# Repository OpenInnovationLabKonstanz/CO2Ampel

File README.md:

# CO2Ampel
A device for visual representation of  CO2 concentraition in the air. Helps monitoring air quality in order to reduce the risk of COVID19 infections in closed rooms.

## Project Overview

ToDo: ...

## Hardware

The device consists of a CO2 sensor, connected to a ESP32-WROOM-32 as main controller. Three large LED arrays (red, yellow, green) are used as a indicator for air quality. In addition, a numeric display shows the current CO2 concentration in ppm.

### CO2 Sensor
Due to the bad availability of CO2 sensors during the COVID19 pandemic, multiple sensor types are supported.
* SenseAir S8 (UART)
* MH-Z19B (pin-compatible to the S8)
* Sensirion SCD30 (I2C)

### Environment Sensor
As an additional method of air quality measurement, a Bosch BME680 multi environmental sensor is used. 
It provides temperature, rel. humidity, air pressure and VOC (volatile organic compounds) measurement.

### Ambient Light Sensor
In order to adapt the display and LED brightness, a OPT3001 ambient light 

### Display
A 4-digit 7-segment display, driven by a TitanMicro TM1638 is used to display the current CO2 concentration (in ppm).

## PCB
The PCB is routed as a 2-layer PCB. Parts are only placed on the top side in order to facilitate mass production.
Layout files are provided as Eagle 6.4 .brd and .sch files.

## Software
The firmware for the ESP32 is written in Arduino, using the ESP32-Arduino support package.
It uses following external libraries:
* SparkFun SCD30 Library (ToDo: Link)
* ClosedCube OPT3001 Library (ToDo: Link)
* Adafruit Sensor Library (ToDo: Link)
* Adafruit BME680 Library (ToDo: Link)
* ...

## Mechanical
The housing is laser-cut from 3mm acrylic sheets. Use sheets with satin finish for better light dispersion (eg. TroGlass Satin).
DXF files for cutting and engraving are provided in *Mechanical*.

## Contact
Stefan Oechslein, Open Innovation Lab Konstanz, oil@htwg-konstanz.de

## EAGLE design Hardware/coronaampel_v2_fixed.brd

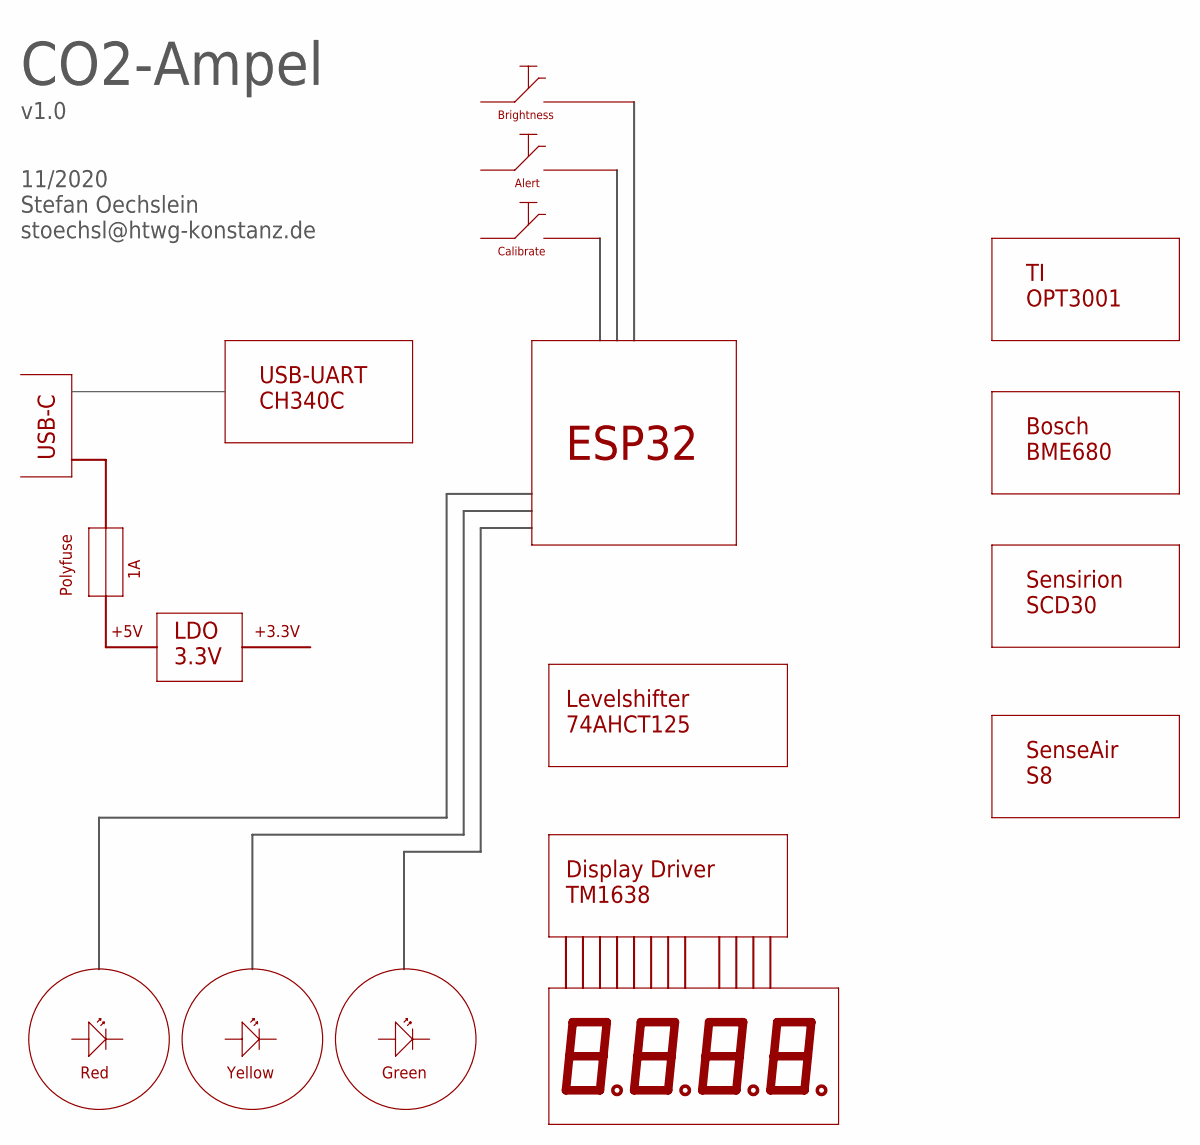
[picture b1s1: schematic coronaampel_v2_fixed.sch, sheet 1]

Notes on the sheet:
CO2-Ampel
ESP32
Sensirion SCD30
SenseAir S8
Bosch BME680
TI OPT3001
USB-UART CH340C
USB-C
LDO 3.3V
Display Driver TM1638
Levelshifter 74AHCT125
Polyfuse
+5V
+3.3V
Red
Yellow
Green
Alert
Calibrate
Brightness
v1.0
11/2020 Stefan Oechslein stoechsl@htwg-konstanz.de

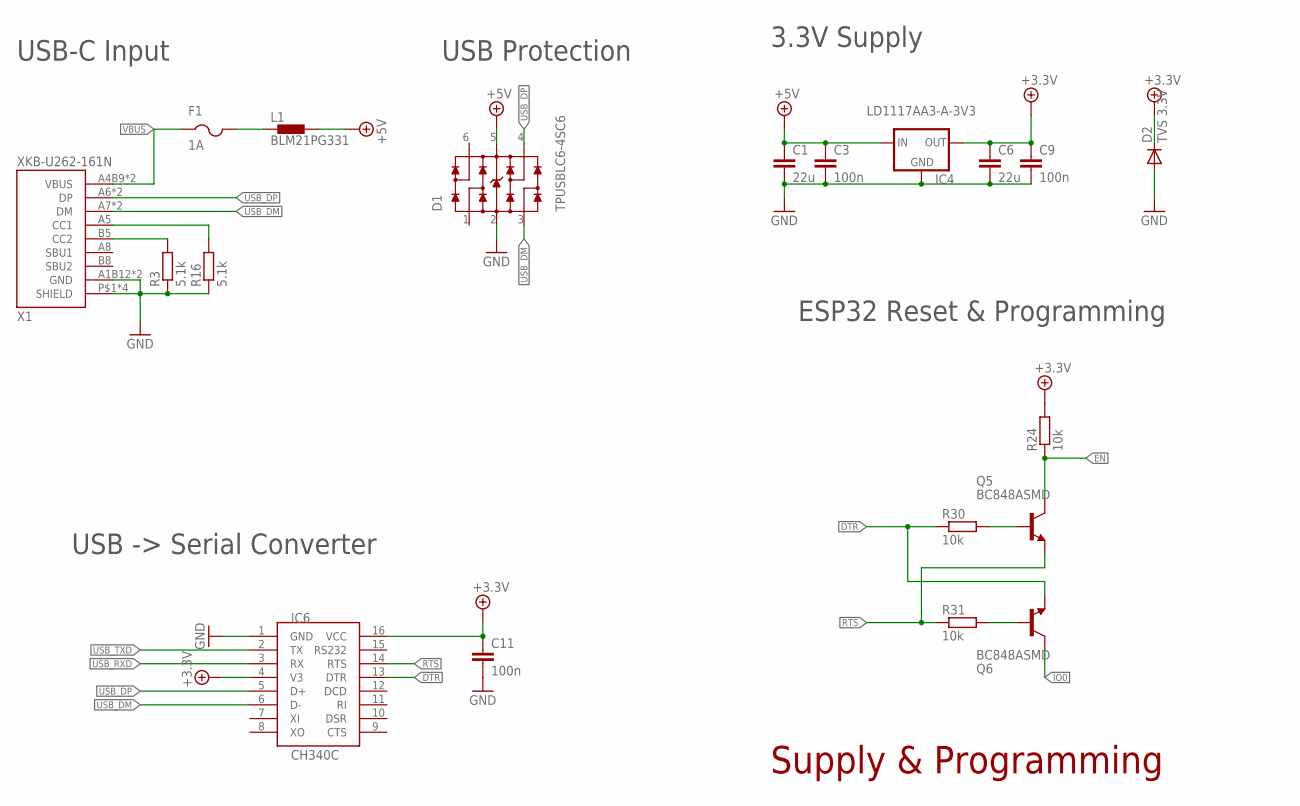
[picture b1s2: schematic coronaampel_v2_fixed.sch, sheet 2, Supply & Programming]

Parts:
C1, C6: 22u; C0805
C3, C9, C11: 100n; C0805
D1: TPUSBLC6-4SC6; WE-TVS_SOT23-6L
D2: TVS 3.3V; SOD123
F1: 1A; R0805
IC4: LD1117AA3-A-3V3; SOT223
IC6: CH340C; SOIC16
L1: BLM21PG331; 0805
Q5, Q6: BC848ASMD; SOT23
R3, R16: 5.1k; R0805
R24, R30, R31: 10k; R0805
X1: XKB-U262-161N; XKB_U262-161N

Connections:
+3,3V: C6.1, C9.1, C11.1, D2.C, IC4.2 (OUT), IC4.4 (OUT), IC6.4 (V3), IC6.16 (VCC), R24.2; also elsewhere on the board
+5V: C1.1, C3.1, D1.5 (VDD), IC4.3 (IN), L1.2; also elsewhere on the board
CC1: R16.2, X1.A5 (CC1)
CC2: R3.2, X1.B5 (CC2)
DTR: IC6.13 (DTR), Q6.2 (E), R30.1
EN: Q5.3 (C), R24.1; also elsewhere on the board
GND: C1.2, C3.2, C6.2, C9.2, C11.2, D1.2 (GND), D2.A, IC4.1 (GND), IC6.1 (GND), R3.1, R16.1, X1.A1B12 (GND), X1.B1A12 (GND), X1.P$1 (SHIELD), X1.P$2 (SHIELD), X1.P$3 (SHIELD), X1.P$4 (SHIELD); also elsewhere on the board
IO0: Q6.3 (C); also elsewhere on the board
unnamed: Q6.1 (B), R31.2
unnamed: Q5.1 (B), R30.2
RTS: IC6.14 (RTS), Q5.2 (E), R31.1
USB_DM: D1.3 (2), IC6.6 (D-), X1.A7 (DM), X1.B7 (DM)
USB_DP: D1.4 (3), IC6.5 (D+), X1.A6 (DP), X1.B6 (DP)
USB_RXD: IC6.3 (RX); also elsewhere on the board
USB_TXD: IC6.2 (TX); also elsewhere on the board
VBUS: F1.1, X1.A4B9 (VBUS), X1.B4A9 (VBUS)
VIN: F1.2, L1.1

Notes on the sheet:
USB -> Serial Converter
ESP32 Reset & Programming
USB-C Input
USB Protection
3.3V Supply
Supply & Programming

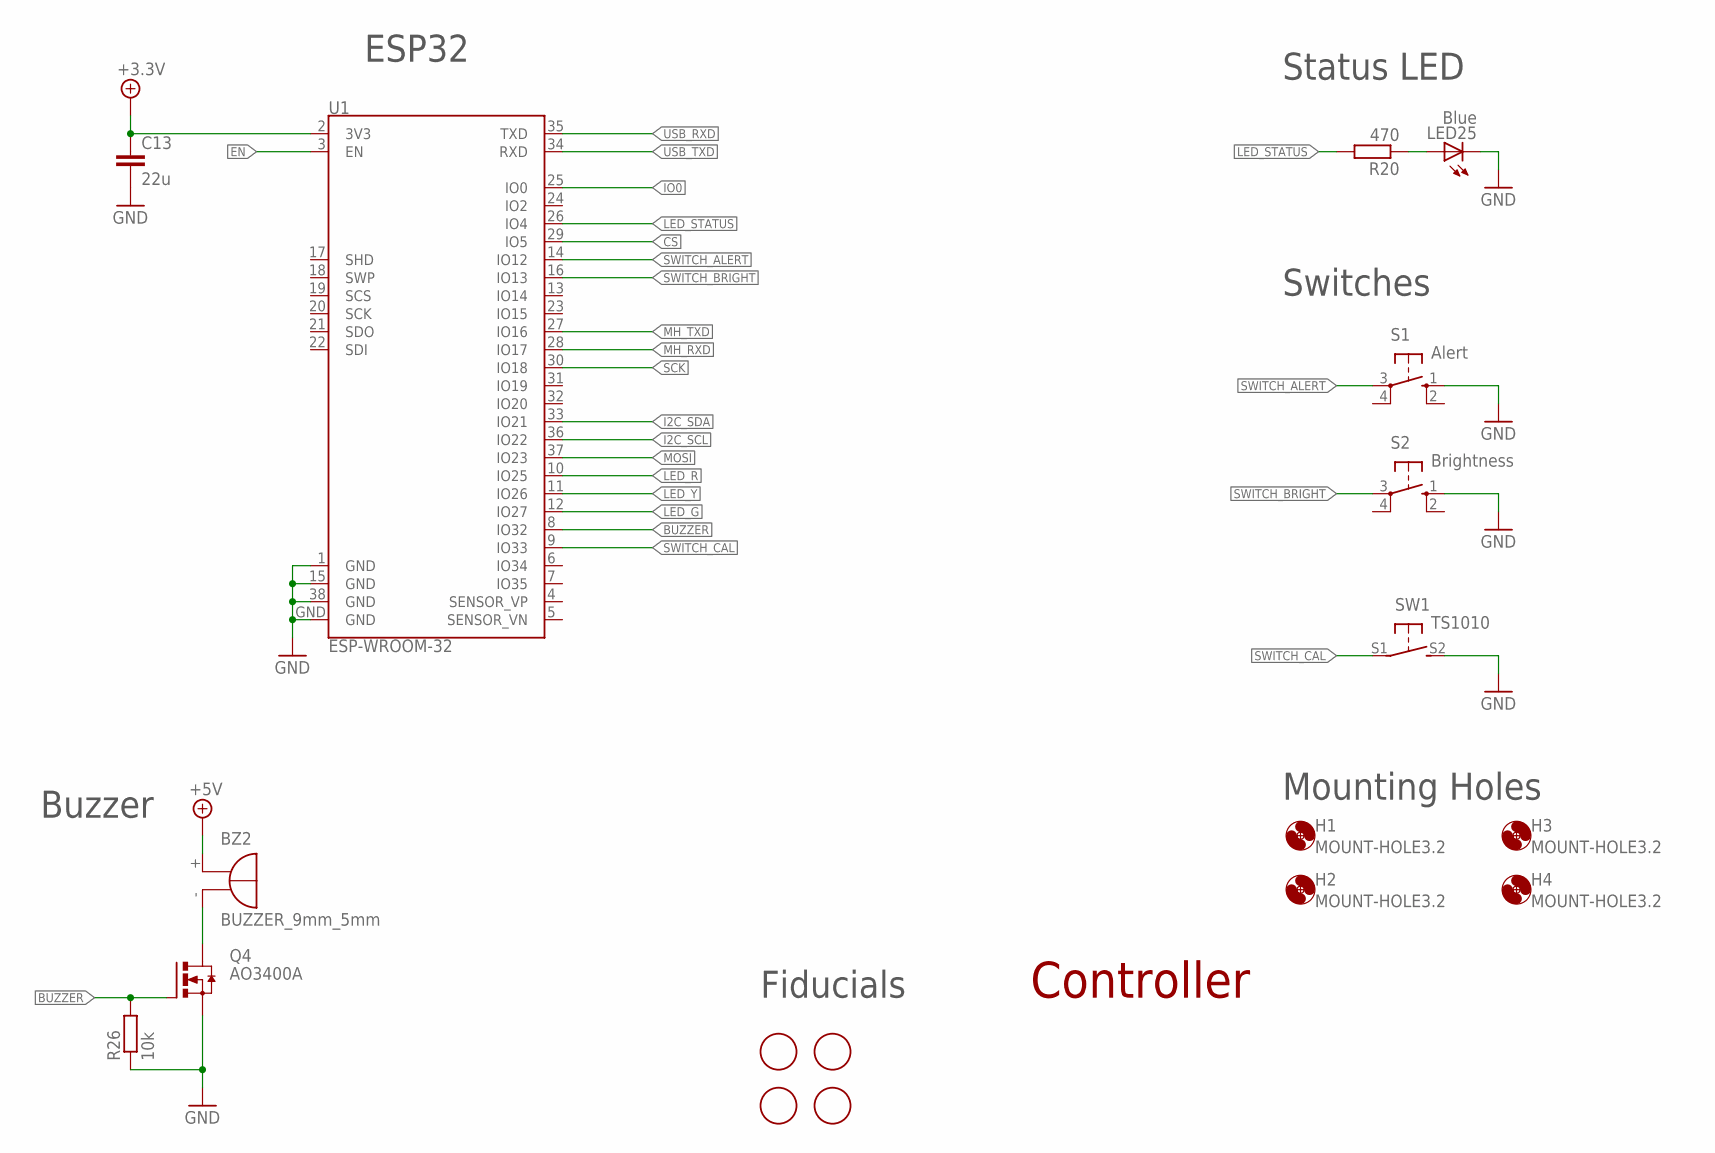
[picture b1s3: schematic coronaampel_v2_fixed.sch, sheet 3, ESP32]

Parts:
BZ2: BUZZER_9mm_5mm; BUZ_9_5
C13: 22u; C0805
H1, H2, H3, H4: MOUNT-HOLE3.2; 3,2
LED25: Blue; CHIPLED_0805
Q4: AO3400A; MICRO3
R20: 470; R0805
R26: 10k; R0805
S1: Alert; B3F-10XX
S2: Brightness; B3F-10XX
SW1: TS1010
U1: ESP-WROOM-32
U$4, U$6, U$7, U$8: FIDUCIAL; FIDUCIAL_1MM

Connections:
+3,3V: C13.1, U1.2 (3V3); also elsewhere on the board
+5V: BZ2.+; also elsewhere on the board
BUZ: BZ2.-, Q4.3 (D)
BUZZER: Q4.1 (G), R26.2, U1.8 (IO32)
CS: U1.29 (IO5); also elsewhere on the board
EN: U1.3 (EN); also elsewhere on the board
GND: C13.2, LED25.C, Q4.2 (S), R26.1, S1.1 (S), S2.1 (S), SW1.S2 (S), U1.1 (GND), U1.15 (GND), U1.38 (GND), U1.GND; also elsewhere on the board
I2C_SCL: U1.36 (IO22); also elsewhere on the board
I2C_SDA: U1.33 (IO21); also elsewhere on the board
IO0: U1.25 (IO0); also elsewhere on the board
LED_G: U1.12 (IO27); also elsewhere on the board
LED_R: U1.10 (IO25); also elsewhere on the board
LED_STATUS: R20.2, U1.26 (IO4)
LED_Y: U1.11 (IO26); also elsewhere on the board
MH_RXD: U1.28 (IO17); also elsewhere on the board
MH_TXD: U1.27 (IO16); also elsewhere on the board
MOSI: U1.37 (IO23); also elsewhere on the board
unnamed: LED25.A, R20.1
SCK: U1.30 (IO18); also elsewhere on the board
SWITCH_ALERT: S1.3, U1.14 (IO12)
SWITCH_BRIGHT: S2.3, U1.16 (IO13)
SWITCH_CAL: SW1.S1, U1.9 (IO33)
USB_RXD: U1.35 (TXD); also elsewhere on the board
USB_TXD: U1.34 (RXD); also elsewhere on the board

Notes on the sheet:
Buzzer
Status LED
Switches
ESP32
Controller
Fiducials
Mounting Holes

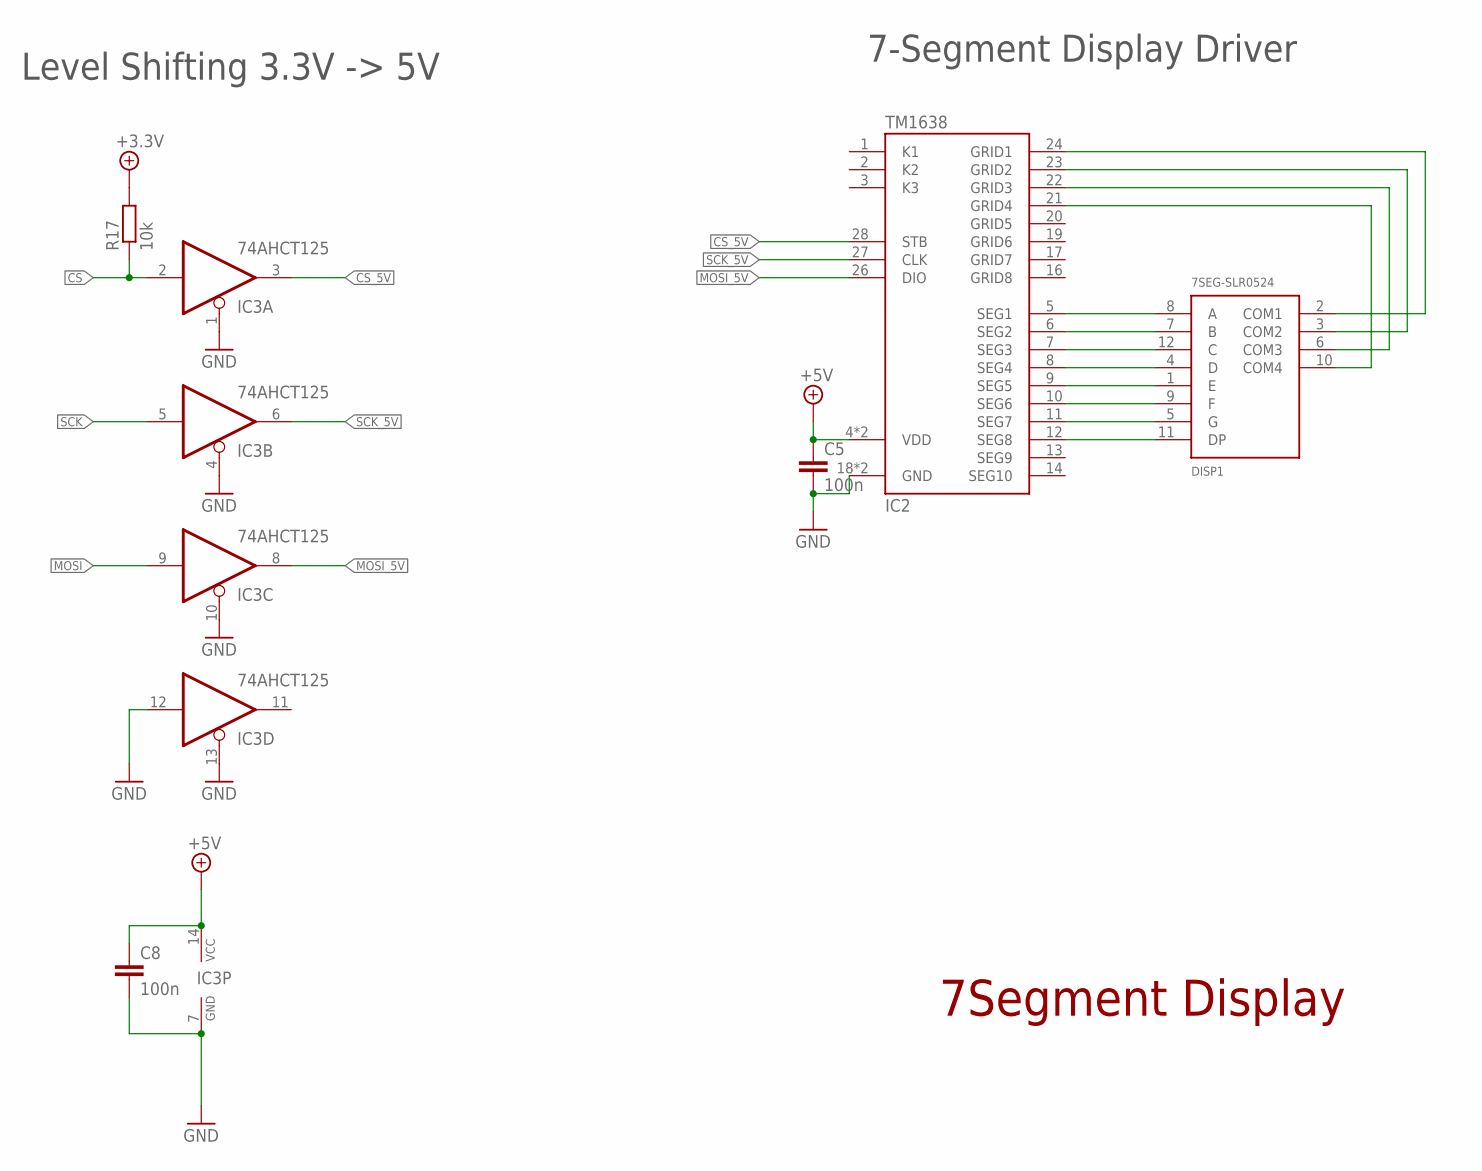
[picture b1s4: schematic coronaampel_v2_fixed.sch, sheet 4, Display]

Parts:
C5, C8: 100n; C0805
DISP1: 7SEG-SLR0524; SEG-SLR0524
IC2: TM1638; SO-28L
IC3: 74AHCT125; TSSOP14
R17: 10k; R0805

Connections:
+3,3V: R17.2; also elsewhere on the board
+5V: C5.1, C8.1, IC2.4 (VDD), IC2.15 (VDD), IC3.14 (VCC); also elsewhere on the board
CS: IC3.2 (I), R17.1; also elsewhere on the board
CS_5V: IC2.28 (STB), IC3.3 (O)
GND: C5.2, C8.2, IC2.18 (GND), IC2.25 (GND), IC3.1 (OE), IC3.4 (OE), IC3.7 (GND), IC3.10 (OE), IC3.12 (I), IC3.13 (OE); also elsewhere on the board
GRID1: DISP1.2 (COM1), IC2.24 (GRID1)
GRID2: DISP1.3 (COM2), IC2.23 (GRID2)
GRID3: DISP1.6 (COM3), IC2.22 (GRID3)
GRID4: DISP1.10 (COM4), IC2.21 (GRID4)
MOSI: IC3.9 (I); also elsewhere on the board
MOSI_5V: IC2.26 (DIO), IC3.8 (O)
SCK: IC3.5 (I); also elsewhere on the board
SCK_5V: IC2.27 (CLK), IC3.6 (O)
SEG1: DISP1.8 (A), IC2.5 (SEG1)
SEG2: DISP1.7 (B), IC2.6 (SEG2)
SEG3: DISP1.12 (C), IC2.7 (SEG3)
SEG4: DISP1.4 (D), IC2.8 (SEG4)
SEG5: DISP1.1 (E), IC2.9 (SEG5)
SEG6: DISP1.9 (F), IC2.10 (SEG6)
SEG7: DISP1.5 (G), IC2.11 (SEG7)
SEG8: DISP1.11 (DP), IC2.12 (SEG8)

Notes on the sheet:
Level Shifting 3.3V -> 5V
7-Segment Display Driver
7Segment Display

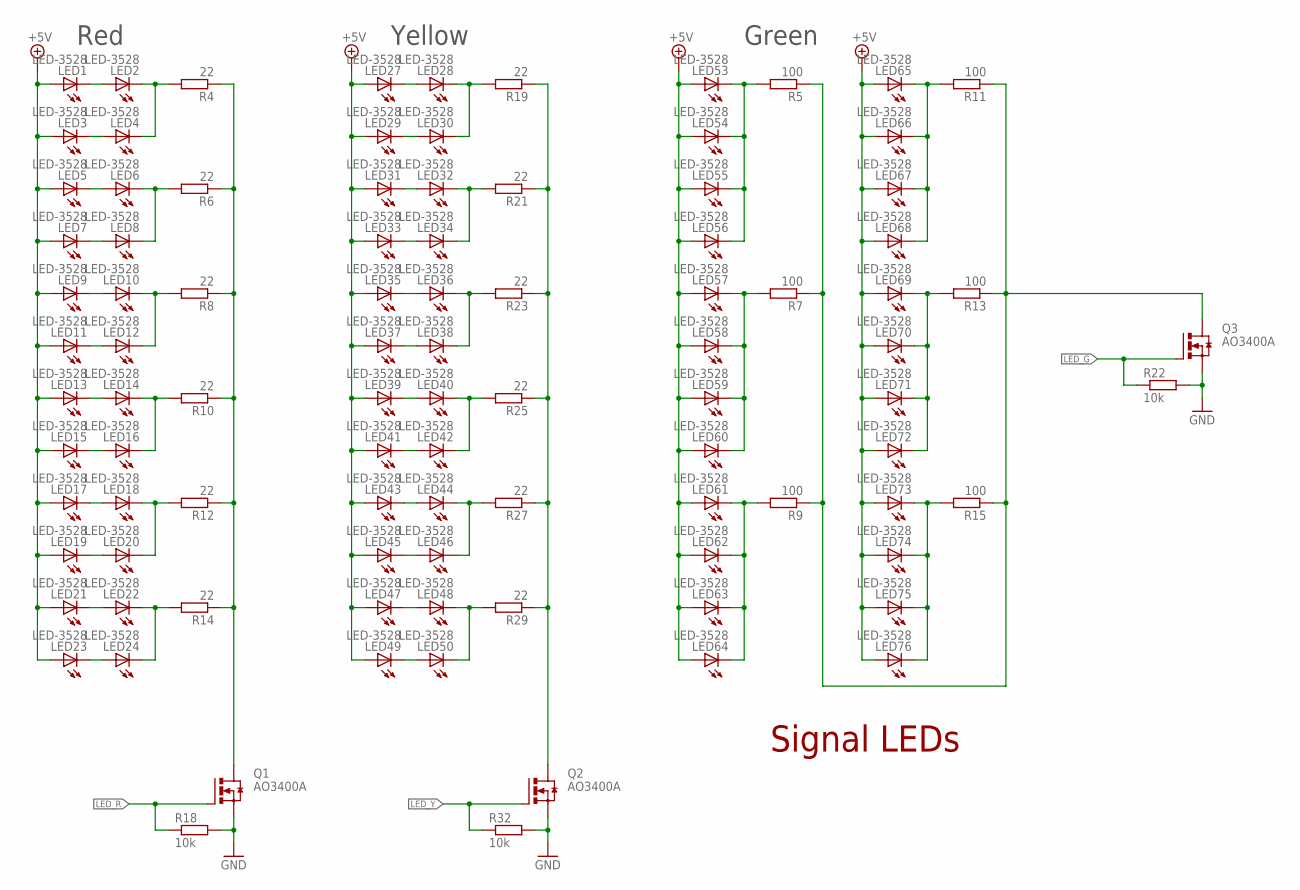
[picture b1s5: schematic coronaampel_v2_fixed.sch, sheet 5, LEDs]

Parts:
LED1, LED2, LED3, LED4, LED5, LED6, LED7, LED8, LED9, LED10, LED11, LED12, LED13, LED14, LED15, LED16, LED17, LED18, LED19, LED20, LED21, LED22, LED23, LED24, LED27, LED28, LED29, LED30, LED31, LED32, LED33, LED34, LED35, LED36, LED37, LED38, LED39, LED40, LED41, LED42, LED43, LED44, LED45, LED46, LED47, LED48, LED49, LED50, LED53, LED54, LED55, LED56, LED57, LED58, LED59, LED60, LED61, LED62, LED63, LED64, LED65, LED66, LED67, LED68, LED69, LED70, LED71, LED72, LED73, LED74, LED75, LED76: LED-3528; 3528
Q1, Q2, Q3: AO3400A; MICRO3
R4, R6, R8, R10, R12, R14, R19, R21, R23, R25, R27, R29: 22; R0805
R5, R7, R9, R11, R13, R15: 100; R0805
R18, R22, R32: 10k; R0805

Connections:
+5V: LED1.A, LED3.A, LED5.A, LED7.A, LED9.A, LED11.A, LED13.A, LED15.A, LED17.A, LED19.A, LED21.A, LED23.A, LED27.A, LED29.A, LED31.A, LED33.A, LED35.A, LED37.A, LED39.A, LED41.A, LED43.A, LED45.A, LED47.A, LED49.A, LED53.A, LED54.A, LED55.A, LED56.A, LED57.A, LED58.A, LED59.A, LED60.A, LED61.A, LED62.A, LED63.A, LED64.A, LED65.A, LED66.A, LED67.A, LED68.A, LED69.A, LED70.A, LED71.A, LED72.A, LED73.A, LED74.A, LED75.A, LED76.A; also elsewhere on the board
GND: Q1.2 (S), Q2.2 (S), Q3.2 (S), R18.2, R22.2, R32.2; also elsewhere on the board
LED_G: Q3.1 (G), R22.1; also elsewhere on the board
LED_G_GND: Q3.3 (D), R5.1, R7.1, R9.1, R11.1, R13.1, R15.1
LED_R: Q1.1 (G), R18.1; also elsewhere on the board
LED_R_GND: Q1.3 (D), R4.1, R6.1, R8.1, R10.1, R12.1, R14.1
LED_Y: Q2.1 (G), R32.1; also elsewhere on the board
LED_Y_GND: Q2.3 (D), R19.1, R21.1, R23.1, R25.1, R27.1, R29.1
unnamed: LED1.C, LED2.A
unnamed: LED3.C, LED4.A
unnamed: LED5.C, LED6.A
unnamed: LED2.C, LED4.C, R4.2
unnamed: LED53.C, LED54.C, LED55.C, LED56.C, R5.2
unnamed: LED6.C, LED8.C, R6.2
unnamed: LED7.C, LED8.A
unnamed: LED9.C, LED10.A
unnamed: LED11.C, LED12.A
unnamed: LED10.C, LED12.C, R8.2
unnamed: LED57.C, LED58.C, LED59.C, LED60.C, R7.2
unnamed: LED13.C, LED14.A
unnamed: LED15.C, LED16.A
unnamed: LED17.C, LED18.A
unnamed: LED14.C, LED16.C, R10.2
unnamed: LED18.C, LED20.C, R12.2
unnamed: LED19.C, LED20.A
unnamed: LED61.C, LED62.C, LED63.C, LED64.C, R9.2
unnamed: LED21.C, LED22.A
unnamed: LED23.C, LED24.A
unnamed: LED22.C, LED24.C, R14.2
unnamed: LED27.C, LED28.A
unnamed: LED29.C, LED30.A
unnamed: LED31.C, LED32.A
unnamed: LED28.C, LED30.C, R19.2
unnamed: LED65.C, LED66.C, LED67.C, LED68.C, R11.2
unnamed: LED32.C, LED34.C, R21.2
unnamed: LED33.C, LED34.A
unnamed: LED35.C, LED36.A
unnamed: LED37.C, LED38.A
unnamed: LED36.C, LED38.C, R23.2
unnamed: LED69.C, LED70.C, LED71.C, LED72.C, R13.2
unnamed: LED39.C, LED40.A
unnamed: LED41.C, LED42.A
unnamed: LED43.C, LED44.A
unnamed: LED40.C, LED42.C, R25.2
unnamed: LED73.C, LED74.C, LED75.C, LED76.C, R15.2
unnamed: LED44.C, LED46.C, R27.2
unnamed: LED45.C, LED46.A
unnamed: LED47.C, LED48.A
unnamed: LED49.C, LED50.A
unnamed: LED48.C, LED50.C, R29.2

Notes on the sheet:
Red
Yellow
Green
Signal LEDs

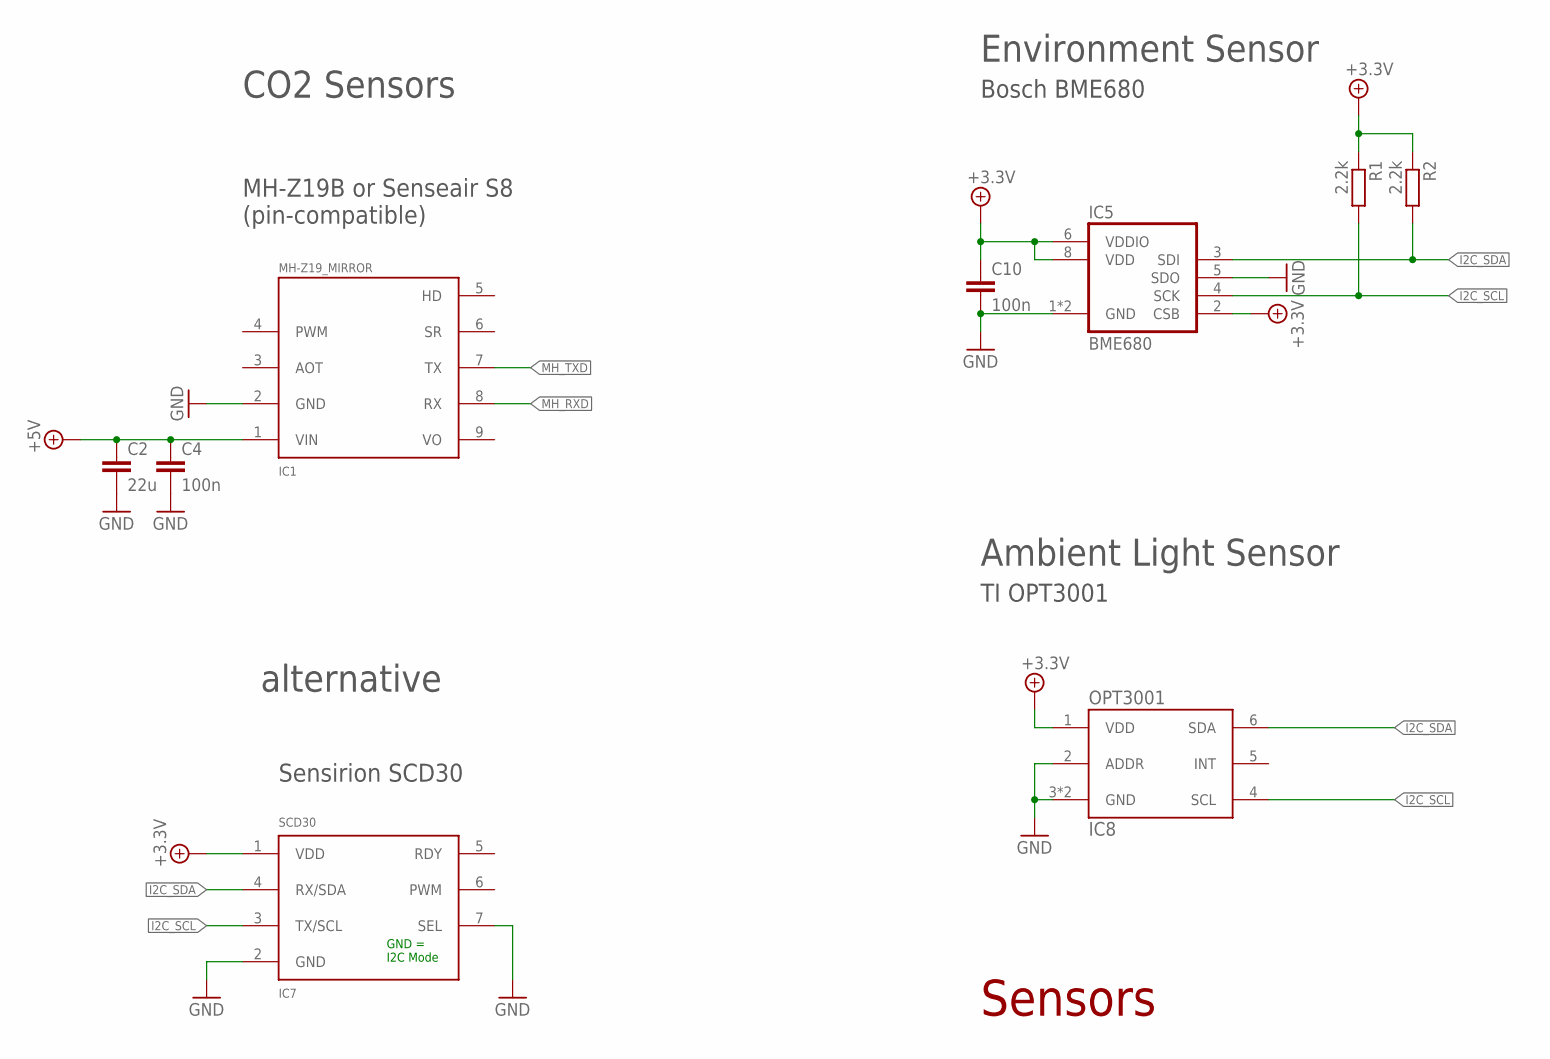
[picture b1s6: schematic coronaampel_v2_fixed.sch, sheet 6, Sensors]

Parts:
C2: 22u; C0805
C4, C10: 100n; C0805
IC1: MH-Z19_MIRROR
IC5: BME680
IC7: SCD30
IC8: OPT3001; USON6
R1, R2: 2.2k; R0805

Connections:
+3,3V: C10.1, IC5.2 (CSB), IC5.6 (VDDIO), IC5.8 (VDD), IC7.1 (VDD), IC8.1 (VDD), R1.1, R2.1; also elsewhere on the board
+5V: C2.1, C4.1, IC1.1 (VIN); also elsewhere on the board
GND: C2.2, C4.2, C10.2, IC1.2 (GND), IC5.1 (GND), IC5.5 (SDO), IC5.7 (GND), IC7.2 (GND), IC7.7 (SEL), IC8.2 (ADDR), IC8.3 (GND), IC8.EP (GND); also elsewhere on the board
I2C_SCL: IC5.4 (SCK), IC7.3 (TX/SCL), IC8.4 (SCL), R1.2; also elsewhere on the board
I2C_SDA: IC5.3 (SDI), IC7.4 (RX/SDA), IC8.6 (SDA), R2.2; also elsewhere on the board
MH_RXD: IC1.8 (RX); also elsewhere on the board
MH_TXD: IC1.7 (TX); also elsewhere on the board

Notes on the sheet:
GND = I2C Mode
CO2 Sensors
MH-Z19B or Senseair S8 (pin-compatible)
Sensirion SCD30
Bosch BME680
TI OPT3001
Ambient Light Sensor
Environment Sensor
Sensors
alternative

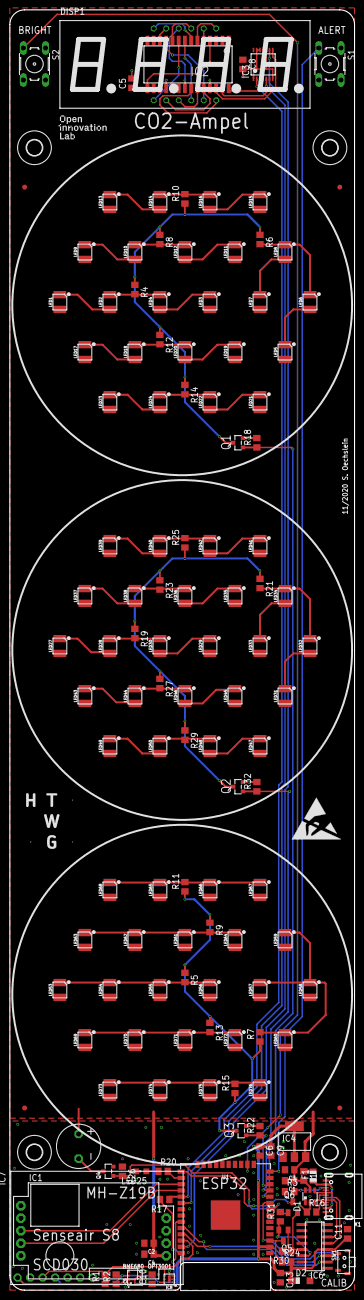
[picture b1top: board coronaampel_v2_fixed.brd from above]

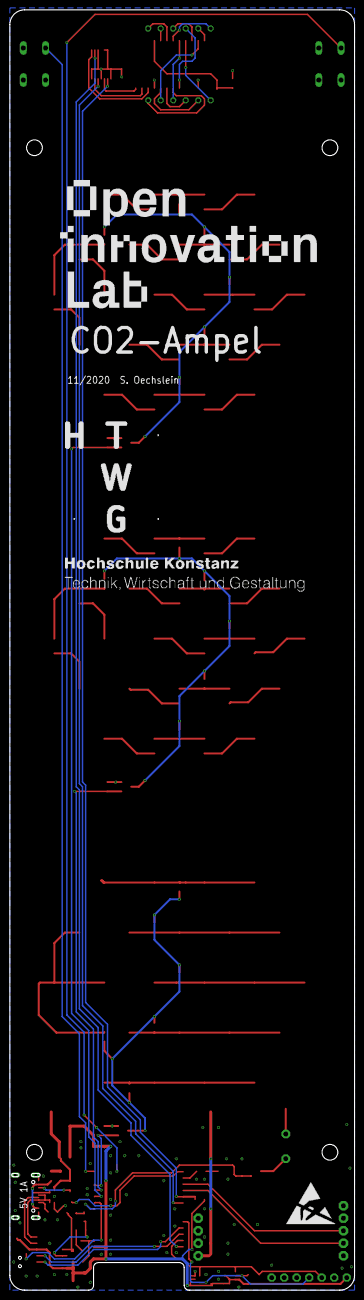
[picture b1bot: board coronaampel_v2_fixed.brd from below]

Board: 2 copper layers, 70.0 x 260.0 mm, 155 parts (4 on the bottom side), 94 nets.

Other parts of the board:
U$1, U$5: ESD_10.00
U$2: OIL_LOGO_10
U$3: OIL_LOGO_50
U$9: HTWG_10
U$10: HTWG_TEXT_8
U$11: HTWG_20

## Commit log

2021-02-02 added readme
2021-02-02 readme
2021-02-02 Added PCB files and schematic
2021-02-02 added documentation
2021-02-02 docu
2021-02-03 fixed board file, added gerbers

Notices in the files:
parts and their libraries:
EagleLibrary_Wuerth_Elektronik_eiSos_rev: Copyright: Würth Elektronik
SparkFun-RF: Licensing: Creative Commons ShareAlike 4.0 International - https://creativecommons.org/licenses/by-sa/4.0
